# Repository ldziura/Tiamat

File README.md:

# Tiamat

The idea behind the Tiamat project is to provide a simple, easy to use, and ergonomic gaming keyboard.
For the moment the project is in a very early stage, but it is already possible to use it.
To spice things up, the Tiamat has an integrated display that doubles as the microcontroller.

<picture>
   <source media="(prefers-color-scheme: light)" srcset="https://github.com/Mqxx/GitHub-Markdown/blob/main/blockquotes/badge/light-theme/warning.svg">
   
</picture><br>

| This is still a very early prototype and the files are constantly changing. It is best to use this repository as a reference instead of a ready to use project. |
|-----------------------------------------------------------------------------------------------------------------------------------------------------------------|

## Features

#### Keyboard features : 

- Ortholinear layout
- Anti Ghosting
- Collumn stagger of the modifier to accomodate for the pinkie
- Thumb cluster for the most used keys
- Smaller spacebar for a better ergonomics
- Stacked numbers and symbols rows for an easier access
- Only the most commonly used keys for gaming
- Hotswap sockets for MX switches

- 240x240 Pin Badge LCD display with backlight that doubles as the microcontroller
- Hotswap sockets for the display

#### Firmware features :

- CircuitPython based firmware
- KMK
- Highly customizable

## Gallery

( All the keys are not final )

## Pin Display

### Polar coordinate snake Game

Complete Snake minigame that uses the polar coordinate system to make the best of the rounded display
Featuring :

- Completely autonomous game, no need to connect the keyboard to a computer only a power source ( you will still need to connect to the Tiamat or another keyboard to play)
- Multiple working menus
- Leaderboard and a highscore system ( stored on the display )
- Screenshot system ( stored on the display )
- And much more ! 

**Click to see on YouTube**
<p align="center" width="100%">
    
</p>

### Animated Wolf

Logo with toggleable animation 

### Gyroscope controlled balls

Gyroscope controlled balls that will are physically simulated and collide with each other as well as the display borders

## Hardware

**WIP**

Display : https://www.waveshare.com/wiki/RP2040-LCD-1.28

## Build

**SOON**

## Firmware

**SOON**

## Credits

- Heavily inspired by Sonal Pinto and his [Mt-Choc](https://github.com/SonalPinto/mt-choc) project and all the ressources he provided
- Aedile for his [CircuitPython Implementation](https://github.com/aedile/circuit_python_wsRP2040128) of the Waveshare RP2040-LCD-1.28 that helped me a lot

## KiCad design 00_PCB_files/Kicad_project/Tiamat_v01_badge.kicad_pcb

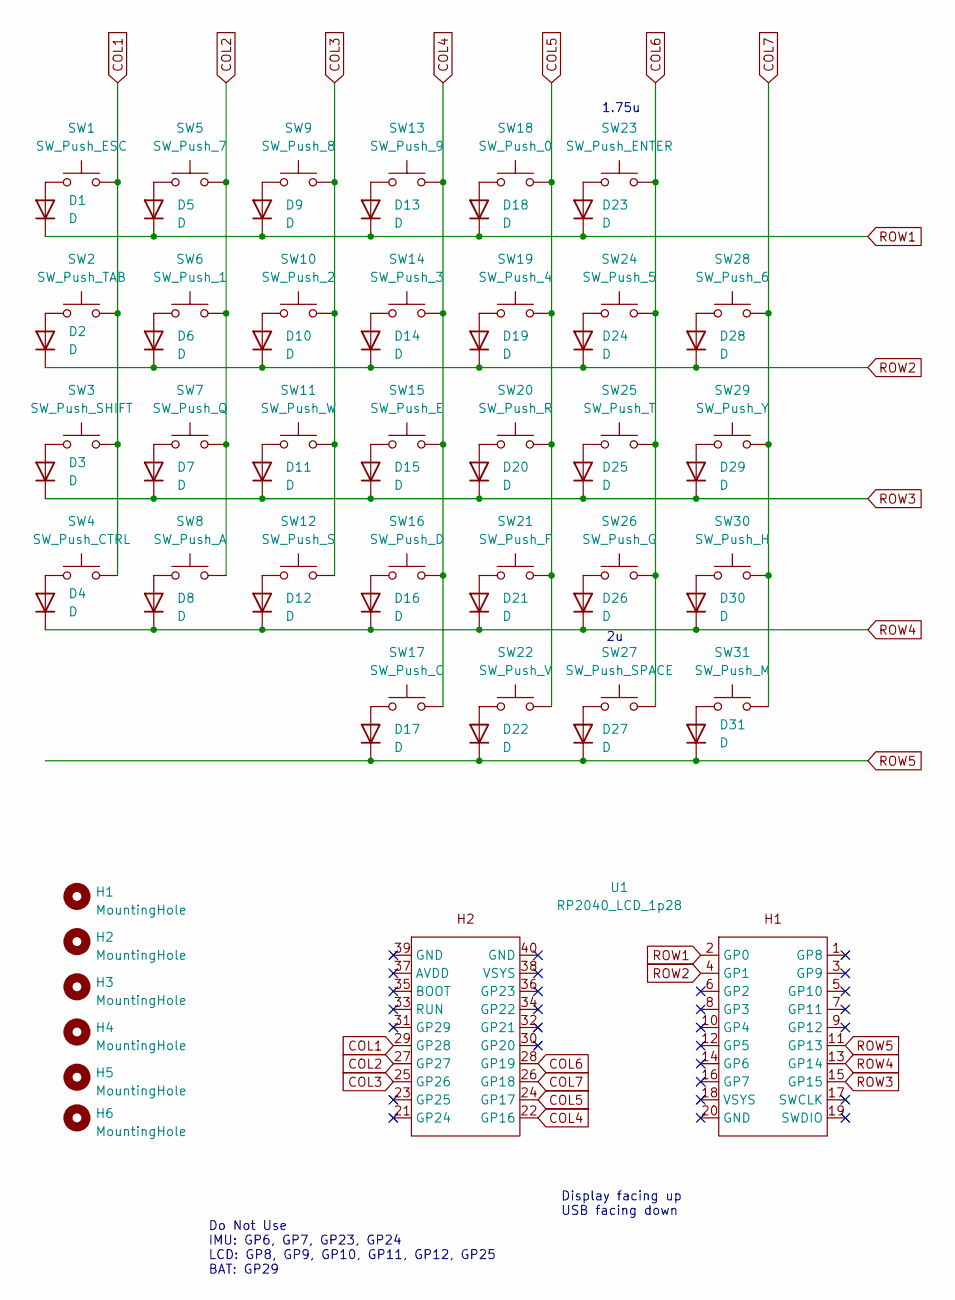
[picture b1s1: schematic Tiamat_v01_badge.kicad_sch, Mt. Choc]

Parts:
D1, D2, D3, D4, D5, D6, D7, D8, D9, D10, D11, D12, D13, D14, D15, D16, D17, D18, D19, D20, D21, D22, D23, D24, D25, D26, D27, D28, D29, D30, D31: D; D_SOD123
H1, H2, H3, H4, H5, H6: MountingHole; m2_standoff
SW1: SW_Push_ESC; MXOnly-1U-Hotswap
SW2: SW_Push_TAB; MXOnly-1U-Hotswap
SW3: SW_Push_SHIFT; MXOnly-1U-Hotswap
SW4: SW_Push_CTRL; MXOnly-1U-Hotswap
SW5: SW_Push_7; MXOnly-1U-Hotswap
SW6: SW_Push_1; MXOnly-1U-Hotswap
SW7: SW_Push_Q; MXOnly-1U-Hotswap
SW8: SW_Push_A; MXOnly-1U-Hotswap
SW9: SW_Push_8; MXOnly-1U-Hotswap
SW10: SW_Push_2; MXOnly-1U-Hotswap
SW11: SW_Push_W; MXOnly-1U-Hotswap
SW12: SW_Push_S; MXOnly-1U-Hotswap
SW13: SW_Push_9; MXOnly-1U-Hotswap
SW14: SW_Push_3; MXOnly-1U-Hotswap
SW15: SW_Push_E; MXOnly-1U-Hotswap
SW16: SW_Push_D; MXOnly-1U-Hotswap
SW17: SW_Push_C; MXOnly-1U-Hotswap
SW18: SW_Push_0; MXOnly-1U-Hotswap
SW19: SW_Push_4; MXOnly-1U-Hotswap
SW20: SW_Push_R; MXOnly-1U-Hotswap
SW21: SW_Push_F; MXOnly-1U-Hotswap
SW22: SW_Push_V; MXOnly-1U-Hotswap
SW23: SW_Push_ENTER; MXOnly-1.75U-Hotswap
SW24: SW_Push_5; MXOnly-1U-Hotswap
SW25: SW_Push_T; MXOnly-1U-Hotswap
SW26: SW_Push_G; MXOnly-1U-Hotswap
SW27: SW_Push_SPACE; MXOnly-2U-Hotswap
SW28: SW_Push_6; MXOnly-1U-Hotswap
SW29: SW_Push_Y; MXOnly-1U-Hotswap
SW30: SW_Push_H; MXOnly-1U-Hotswap
SW31: SW_Push_M; MXOnly-1U-Hotswap
U1: RP2040_LCD_1p28

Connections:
COL1: SW1.2, SW2.2, SW3.2, SW4.2, U1.29 (GP28)
COL2: SW5.2, SW6.2, SW7.2, SW8.2, U1.27 (GP27)
COL3: SW9.2, SW10.2, SW11.2, SW12.2, U1.25 (GP26)
COL4: SW13.2, SW14.2, SW15.2, SW16.2, SW17.2, U1.22 (GP16)
COL5: SW18.2, SW19.2, SW20.2, SW21.2, SW22.2, U1.24 (GP17)
COL6: SW23.2, SW24.2, SW25.2, SW26.2, SW27.2, U1.28 (GP19)
COL7: SW28.2, SW29.2, SW30.2, SW31.2, U1.26 (GP18)
unnamed: D1.2 (A), SW1.1
unnamed: D2.2 (A), SW2.1
unnamed: D3.2 (A), SW3.1
unnamed: D4.2 (A), SW4.1
unnamed: D5.2 (A), SW5.1
unnamed: D6.2 (A), SW6.1
unnamed: D7.2 (A), SW7.1
unnamed: D8.2 (A), SW8.1
unnamed: D9.2 (A), SW9.1
unnamed: D10.2 (A), SW10.1
unnamed: D11.2 (A), SW11.1
unnamed: D12.2 (A), SW12.1
unnamed: D13.2 (A), SW13.1
unnamed: D14.2 (A), SW14.1
unnamed: D15.2 (A), SW15.1
unnamed: D16.2 (A), SW16.1
unnamed: D17.2 (A), SW17.1
unnamed: D18.2 (A), SW18.1
unnamed: D19.2 (A), SW19.1
unnamed: D20.2 (A), SW20.1
unnamed: D21.2 (A), SW21.1
unnamed: D22.2 (A), SW22.1
unnamed: D23.2 (A), SW23.1
unnamed: D24.2 (A), SW24.1
unnamed: D25.2 (A), SW25.1
unnamed: D26.2 (A), SW26.1
unnamed: D27.2 (A), SW27.1
unnamed: D28.2 (A), SW28.1
unnamed: D29.2 (A), SW29.1
unnamed: D30.2 (A), SW30.1
unnamed: D31.2 (A), SW31.1
ROW1: D1.1 (K), D5.1 (K), D9.1 (K), D13.1 (K), D18.1 (K), D23.1 (K), U1.2 (GP0)
ROW2: D2.1 (K), D6.1 (K), D10.1 (K), D14.1 (K), D19.1 (K), D24.1 (K), D28.1 (K), U1.4 (GP1)
ROW3: D3.1 (K), D7.1 (K), D11.1 (K), D15.1 (K), D20.1 (K), D25.1 (K), D29.1 (K), U1.15 (GP15)
ROW4: D4.1 (K), D8.1 (K), D12.1 (K), D16.1 (K), D21.1 (K), D26.1 (K), D30.1 (K), U1.13 (GP14)
ROW5: D17.1 (K), D22.1 (K), D27.1 (K), D31.1 (K), U1.11 (GP13)

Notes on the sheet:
Do Not Use IMU: GP6, GP7, GP23, GP24 LCD: GP8, GP9, GP10, GP11, GP12, GP25 BAT: GP29
1.75u
Display facing up USB facing down

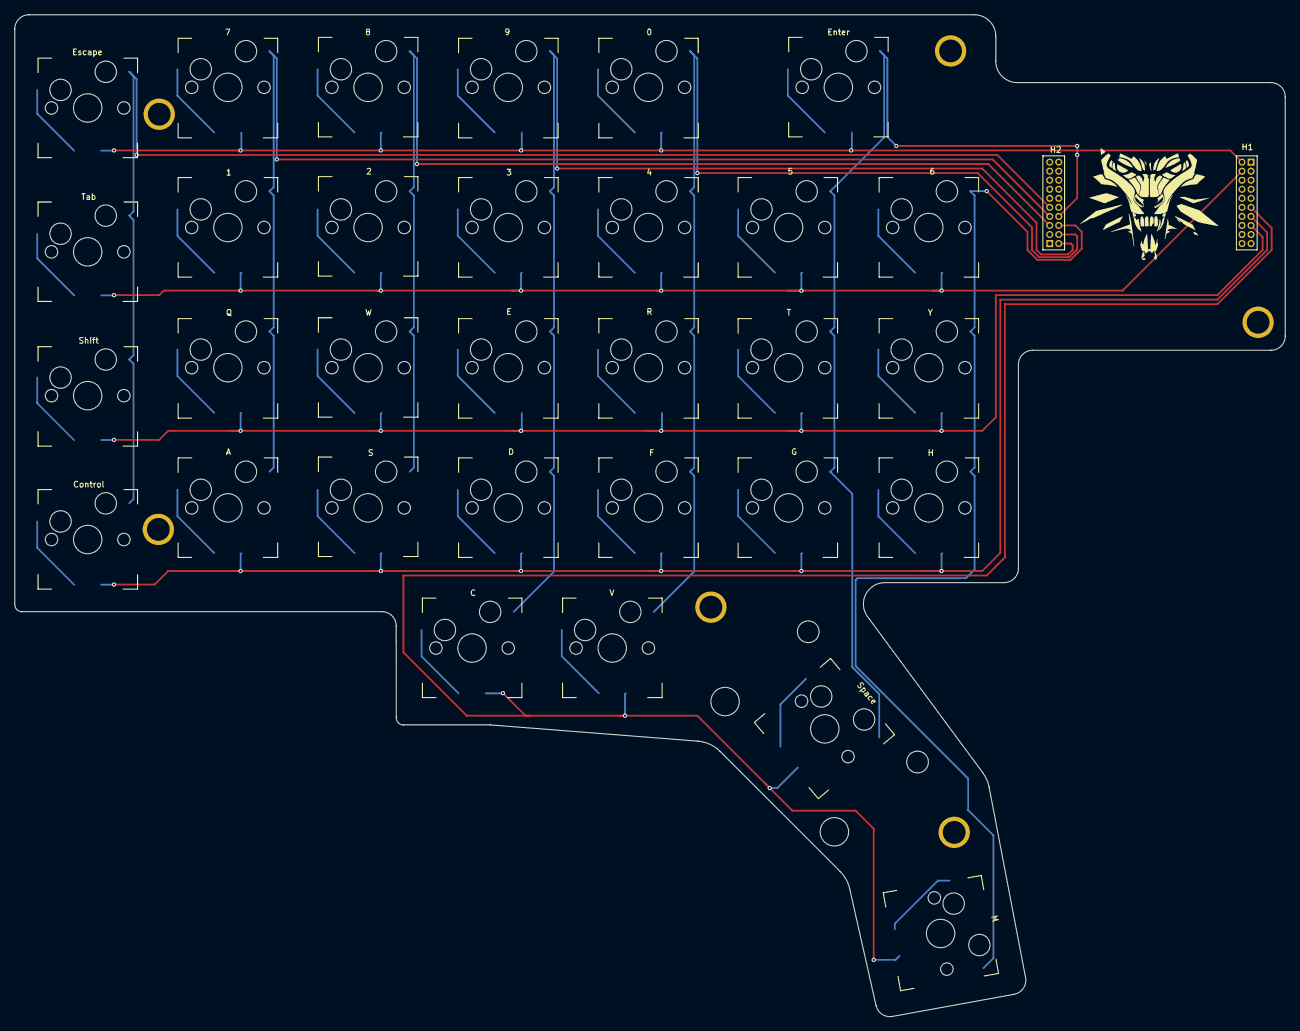
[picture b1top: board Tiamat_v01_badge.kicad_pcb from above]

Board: 2 copper layers, 178.4 x 140.7 mm, 69 parts (0 on the bottom side), 43 nets.

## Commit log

2023-04-11 Readme update
2023-04-11 Create LICENSE

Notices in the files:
00_PCB_files/Kicad_project/Tiamat_v01_badge.kicad_sch:
License: MIT
